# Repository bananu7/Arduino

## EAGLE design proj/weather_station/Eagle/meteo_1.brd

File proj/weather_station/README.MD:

# Weather station project

This is a large-ish project as it involves 4 big parts to integrate:

* An MCU, obviously. Started with ATTiny 2313A, moved to ATMega328p. See MCU section for details.
* Bosch BME280 evnironment sensor - doing humidity, temperature and pressure readings, all at the same time. This a new, state-of-the art sensor, but that requires a breakout board, as the package is super small.
* Winbond W25Q80BV flash memory. This is a 1MB flash memory that can be used for datalogging. It only supports clearing entire pages, but individual bytes can be written and added, which makes it very good for appending small amounts of data.
* NRF24L01 wireless module. Still not integrated. Could possibly be used for gathering data.

## MCU choice

I couldn't make the prototype on the Uno, because pretty much all the external components require 3V3. Thus, I made a 2313 breakout board.
This worked well with one thing, however its limited memory meant that i could fit all the drivers. The BME sensor driver was particularly large.

That prompted the move to ATMega. I made another breakout and so far this is as far as I got; with the software able to read the sensor data and store it in the flash memory.

## Development log

* I've managed to either destroy or buy problematic Flash (that didn't hurt) and a mega (that hurt way more).
* As far as programming the Mega, I started doing non-bootloader loading, but quickly realized it's actually much less convenient than with a bootloader. As a reminder, a bootloader runs before your code (slowing down startup a bit), but allows you to load a program via serial. This means i just need 5 wires hooked up to get both programming and serial capabilities, which is really convenient.
* In order to enable booting from bootloader (and in fact putting it on there), a chip needs to be connected to an SPI AVRISP-like programmer to burn the correct fuse values in and transfer the bootloader code. The bootloader binary is in the repo.

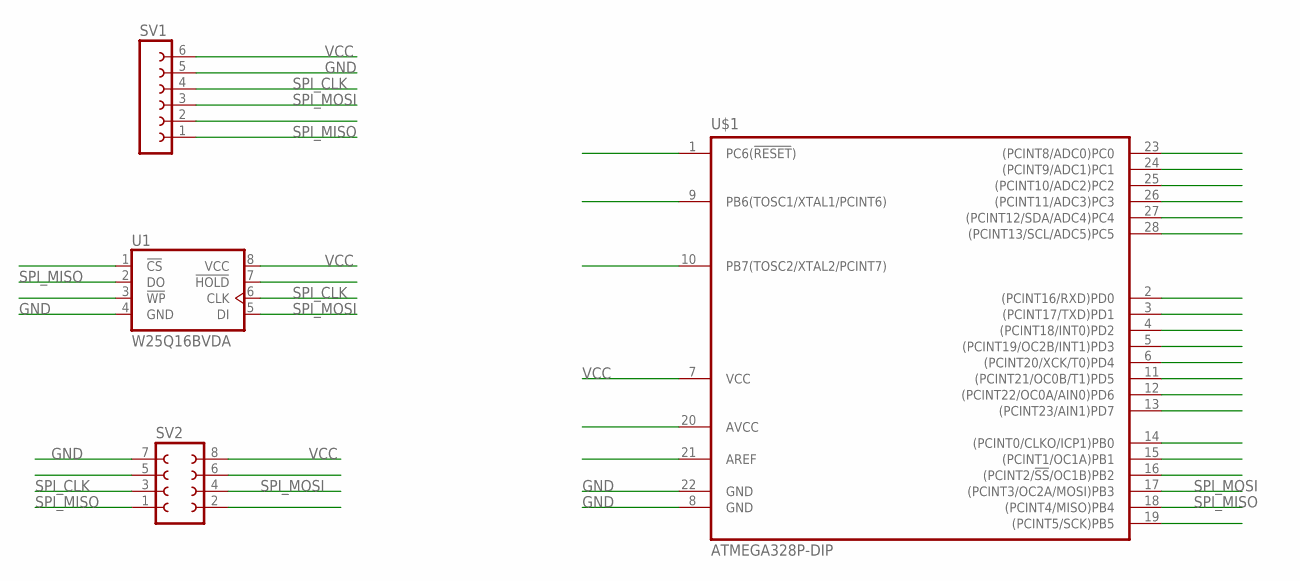
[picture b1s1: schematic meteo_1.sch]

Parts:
SV1: FE06-1; FE06
SV2: FE04-2
U1: W25Q16BVDA; DIL08
U$1: ATMEGA328P-DIP; DIP762W53P254L3500H508Q28B

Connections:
GND: SV1.5, SV2.7, U1.4 (GND), U$1.8 (GND), U$1.22 (GND)
SPI_CLK: SV1.4, SV2.3, U1.6 (CLK)
SPI_MISO: SV1.1, SV2.1, U1.2 (DO), U$1.18 ((PCINT4/MISO)PB4)
SPI_MOSI: SV1.3, SV2.4, U1.5 (DI), U$1.17 ((PCINT3/OC2A/MOSI)PB3)
VCC: SV1.6, SV2.8, U1.8 (VCC), U$1.7 (VCC)

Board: 2 copper layers, 4 parts (0 on the bottom side), 5 nets, no tracks yet.

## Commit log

2016-08-06 Some initial drafts
2016-10-09 Added 7seg bitbang
2016-10-09 Added other nice sketches
2016-10-09 Added the first attempt at modularity
2016-10-09 Added example project that connects to KSP SerialIO plugin
2016-10-09 Some first refactorings
2016-10-09 Some more cleaning and more logical placement of things
2016-10-09 Moved the connected check out
2016-10-09 Fixed compilation errors
2016-10-09 Fixed the serial read problem with the state of the result
2016-11-14 Some changes, not sure exactly what will look later
2016-11-14 Moved maxim files to proper place
2016-11-14 Added lcd bitbang setup
2016-11-14 Added modular spi support - super early, but works
2016-11-14 Moved 7seg files to appropriate places
2016-11-14 Moved HardwareSpi to the separate lib directory
2016-11-14 Even more refactorings in communication
2016-11-14 Improved the Sender a bit
2016-11-15 Some improvements to the library, now it's kinda functional
2016-11-15 A clock! And platformIO support
2016-11-15 Changed sender to a pimpl wrapper so that it doesn't require the user to template over it. Changed arduino fw to a proper main.
2016-11-15 Added broken HD74480 impl
2016-11-15 Split up the HD44780 support into direct and spi classes
2016-11-15 Removed old tryouts
2016-11-15 Renamed the lcd library to a proper name and made it build
2016-11-15 Some rollback changes that basically make the thing work
2016-11-16 Added another pin for the multiplexer disable
2016-11-16 Made LCDs Write public
2016-11-20 Cleanup; made ksp code use new library
2016-11-20 Some small improvementrs
2016-11-20 Added a simple spi_in example for future ref
2016-11-20 Some improvements to the max7219 support library
2020-02-08 Added L6 floorboard
2020-02-08 Added first DIYLC sketch - attiny2313a host board WIP
2020-02-18 Added two small DIYLC files
2020-02-18 improvements to the atmega board
2020-02-22 Reorg
2020-02-22 Added some notes
2020-02-22 Added early draft of winbond memory handling
2020-02-22 Added arduino defs for my standalone megas
2020-02-22 Moved code to PlatformIO
2020-02-23 Added the bme driver and improved serial command parsing
2020-02-23 Both modules now work together; extracted argument parsing to a separate file
2020-02-23 Added early time handling
2020-02-23 Added periodic saving - one sample per page right now
2020-08-19 Added a note about bluepills
2020-08-21 Added first iteration of working spotibox
2020-08-21 Added improved driver that accepts all kinds of stuff and a spotify driver that sends current song to it
2020-08-28 Added my first bare-metal ARM thing
2020-11-07 Added first notes about the 6502 project
2020-11-07 Fixed table
2020-11-07 Fixed PDF link
2020-11-07 Improved parts table again
2020-11-10 Added CPU datasheet link
2021-01-24 Added the updated spotibox code
2021-09-19 Added floorboard schematic
2021-12-30 Added new version of spotibox on Pi
2021-12-30 Removed ansible stuff, replaced with a simple deploy script
2021-12-30 Added the real nginx config
2021-12-30 Hopefully fixed the static issues

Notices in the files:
parts and their libraries:
atmel-avr: Copyright (C) 2008, Bob Starr
memory-winbond: Copyright (C) 2010, Bob Starr
